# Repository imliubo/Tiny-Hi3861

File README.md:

# Tiny-Hi3861

Tiny-Hi3861应该是目前(2020-10-19)最小一款支持鸿蒙OS的开发板了。

有关Hi3861开发板的更多信息可以查看这里：

[Hi3861开发文档](https://gitee.com/openharmony/docs/blob/master/quick-start/Hi3861%E5%BC%80%E5%8F%91%E6%9D%BF.md)

有关丝印为LV的Hi3861芯片暂时没法运行官方例程可以关注这里：

[Hi3861LV版本芯片问题](https://gitee.com/openharmony/docs/issues/I1YQ05?from=project-issue)

目前芯片貌似没有渠道可以直接拿货，或许过段时间应该就...   祝大家玩的愉快！

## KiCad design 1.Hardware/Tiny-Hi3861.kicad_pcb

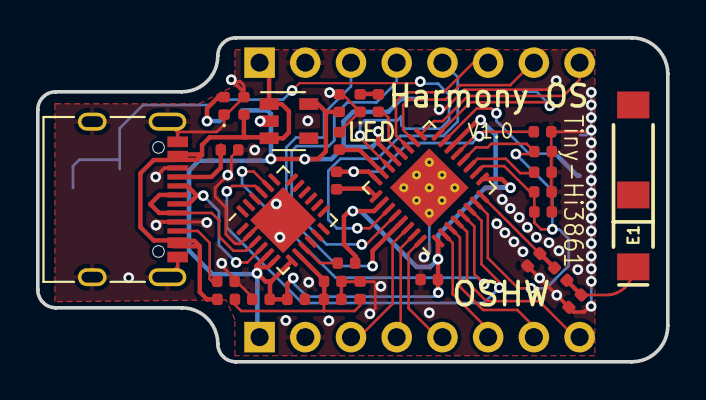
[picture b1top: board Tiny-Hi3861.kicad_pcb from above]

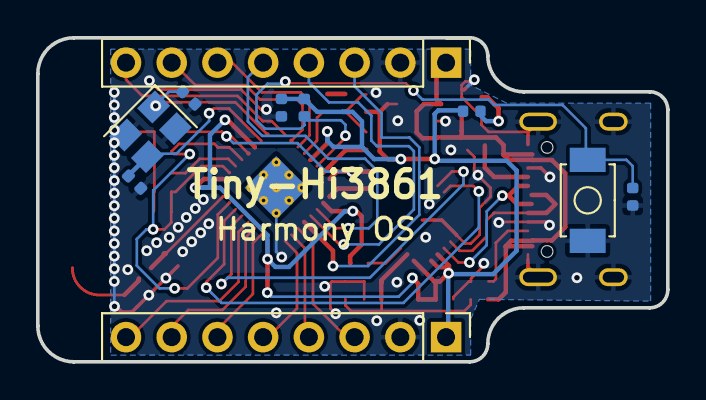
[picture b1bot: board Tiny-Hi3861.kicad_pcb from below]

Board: 2 copper layers, 35.0 x 18.0 mm, 40 parts (10 on the bottom side), 36 nets.

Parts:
C1, C9, C12: 106; C_0402_1005Metric
C2, C3: 22P; C_0402_1005Metric
C4: 4.7uF; C_0402_1005Metric
C5, C6, C7, C10, C11, C13, C14, C17: 104; C_0402_1005Metric
C15, C16: TBD; C_0402_1005Metric
C18: 102; C_0402_1005Metric
C19, C20: 105; C_0402_1005Metric
D2: LED; LED_0402_1005Metric
E1: ANTENNA-RainSun-2.4G; ANT-2.4GHZ-9.5X2.0MM
J1, J2: Conn_01x08_Male; PinHeader_1x08_P2.54mm_Vertical
J3: USB_C_Receptacle_USB2.0; USB_C_Receptacle_XKB_U262-16XN-4BVC11
K1: Mini-Button-3x4x2; Button_2Pin_3x4x2
L1: 2.2uH; L_0402_1005Metric
L2: TBD; L_0402_1005Metric
PWR1: LED/RED; LED_0402_1005Metric
R1: 100K; R_0402_1005Metric
R2: 22K; R_0402_1005Metric
R3: 47K; R_0402_1005Metric
R4, R7, R8: 1K; R_0402_1005Metric
R5, R6: 5.1K; R_0402_1005Metric
U1: Hi3861LV100; QFN-32-1EP_5x5mm_P0.5mm_EP3.1x3.1mm_ThermalVias
U2: HX9193-33GB; SOT-23-5
U3: CP2102N-A01-GQFN24; QFN-24-1EP_4x4mm_P0.5mm_EP2.6x2.6mm
Y1: Crystal_GND24_Small; Crystal_SMD_TXC_7M-4Pin_3.2x2.5mm

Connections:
+3V3: C1.2, C7.2, C9.1, C11.2, C14.1, J2.1, R1.1, R4.1, R7.2, U1.1, U1.9, U1.14, U1.21, U1.26, U2.5, U3.5, U3.6, U3.7
+5V: C10.1, J1.1, J3.A4, J3.A9, J3.B4, J3.B9, R2.2, U2.1, U2.3
/DN: J3.A7, J3.B7, U3.4
/DP: J3.A6, J3.B6, U3.3
/GPIO0: J2.6, U1.2
/GPIO1: J2.7, U1.3
/GPIO2: J2.8, U1.4
/GPIO5: J1.8, U1.17
/GPIO6: J1.7, U1.18
/GPIO7: J1.6, U1.19
/GPIO8: R8.2, U1.20
/GPIO9: J1.5, U1.27
/GPIO10: J1.4, U1.28
/GPIO11: J1.3, U1.29
/GPIO12: J2.3, U1.30
/GPIO13: J2.4, U1.31
/GPIO14: J2.5, U1.32
/RST: C5.2, K1.A, R1.2, U1.22
/RX: U1.6, U3.21
/TX: U1.5, U3.20
/VDD_BUCK_1P3: C4.2, L1.2, U1.13, U1.24
/VDD_PMU_RFLDO1: C17.2, C18.1, C20.2, U1.7, U1.10, U1.12
/XIN: C2.1, U1.16, Y1.1
/XOUT: C3.1, U1.15, Y1.3
GND: C1.1, C2.2, C3.2, C4.1, C5.1, C6.1, C7.1, C9.2, C10.2, C11.1, C12.2, C13.1, C14.2, C15.2, C16.2, C17.1, C18.2, C19.2, C20.1, D2.1, J1.2, J2.2, J3.A1, J3.A8, J3.A12, J3.B1, J3.B8, J3.B12, J3.S1, K1.K, PWR1.1, R3.2, R5.1, R6.1, U1.33, U2.2, U3.2, U3.25, Y1.2, Y1.4
unnamed: C6.2, U1.23
unnamed: C12.1, C13.2, R2.1, R3.1, U3.8
unnamed: C15.1, E1.FEED, L2.1
unnamed: C16.1, L2.2, U1.8
unnamed: C19.1, U1.11
unnamed: D2.2, R8.1
unnamed: J3.A5, R5.2
unnamed: J3.B5, R6.2
unnamed: L1.1, U1.25
unnamed: PWR1.2, R7.1
unnamed: R4.2, U3.9

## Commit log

2020-10-19 ./README.md: 增加部分描述。
2020-10-19 all: 第一版本硬件。
2020-10-19 修改图片。
2020-10-19 修改部分描述。
